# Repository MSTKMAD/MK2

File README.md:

# Proyecto de Contruccion del 2º modelo de la MACHETE (MK2)

Este reopsitorio es un Fork qe proviene del respositorio de bitbucket de la EDCPSU.
Las versiones HW de partida son la r15 para la tarjeta de la EDCPSU
Las versiones SW de partida son la 730 para el codigo de la DUAL y la version 731 de la EDCPSU o Main.

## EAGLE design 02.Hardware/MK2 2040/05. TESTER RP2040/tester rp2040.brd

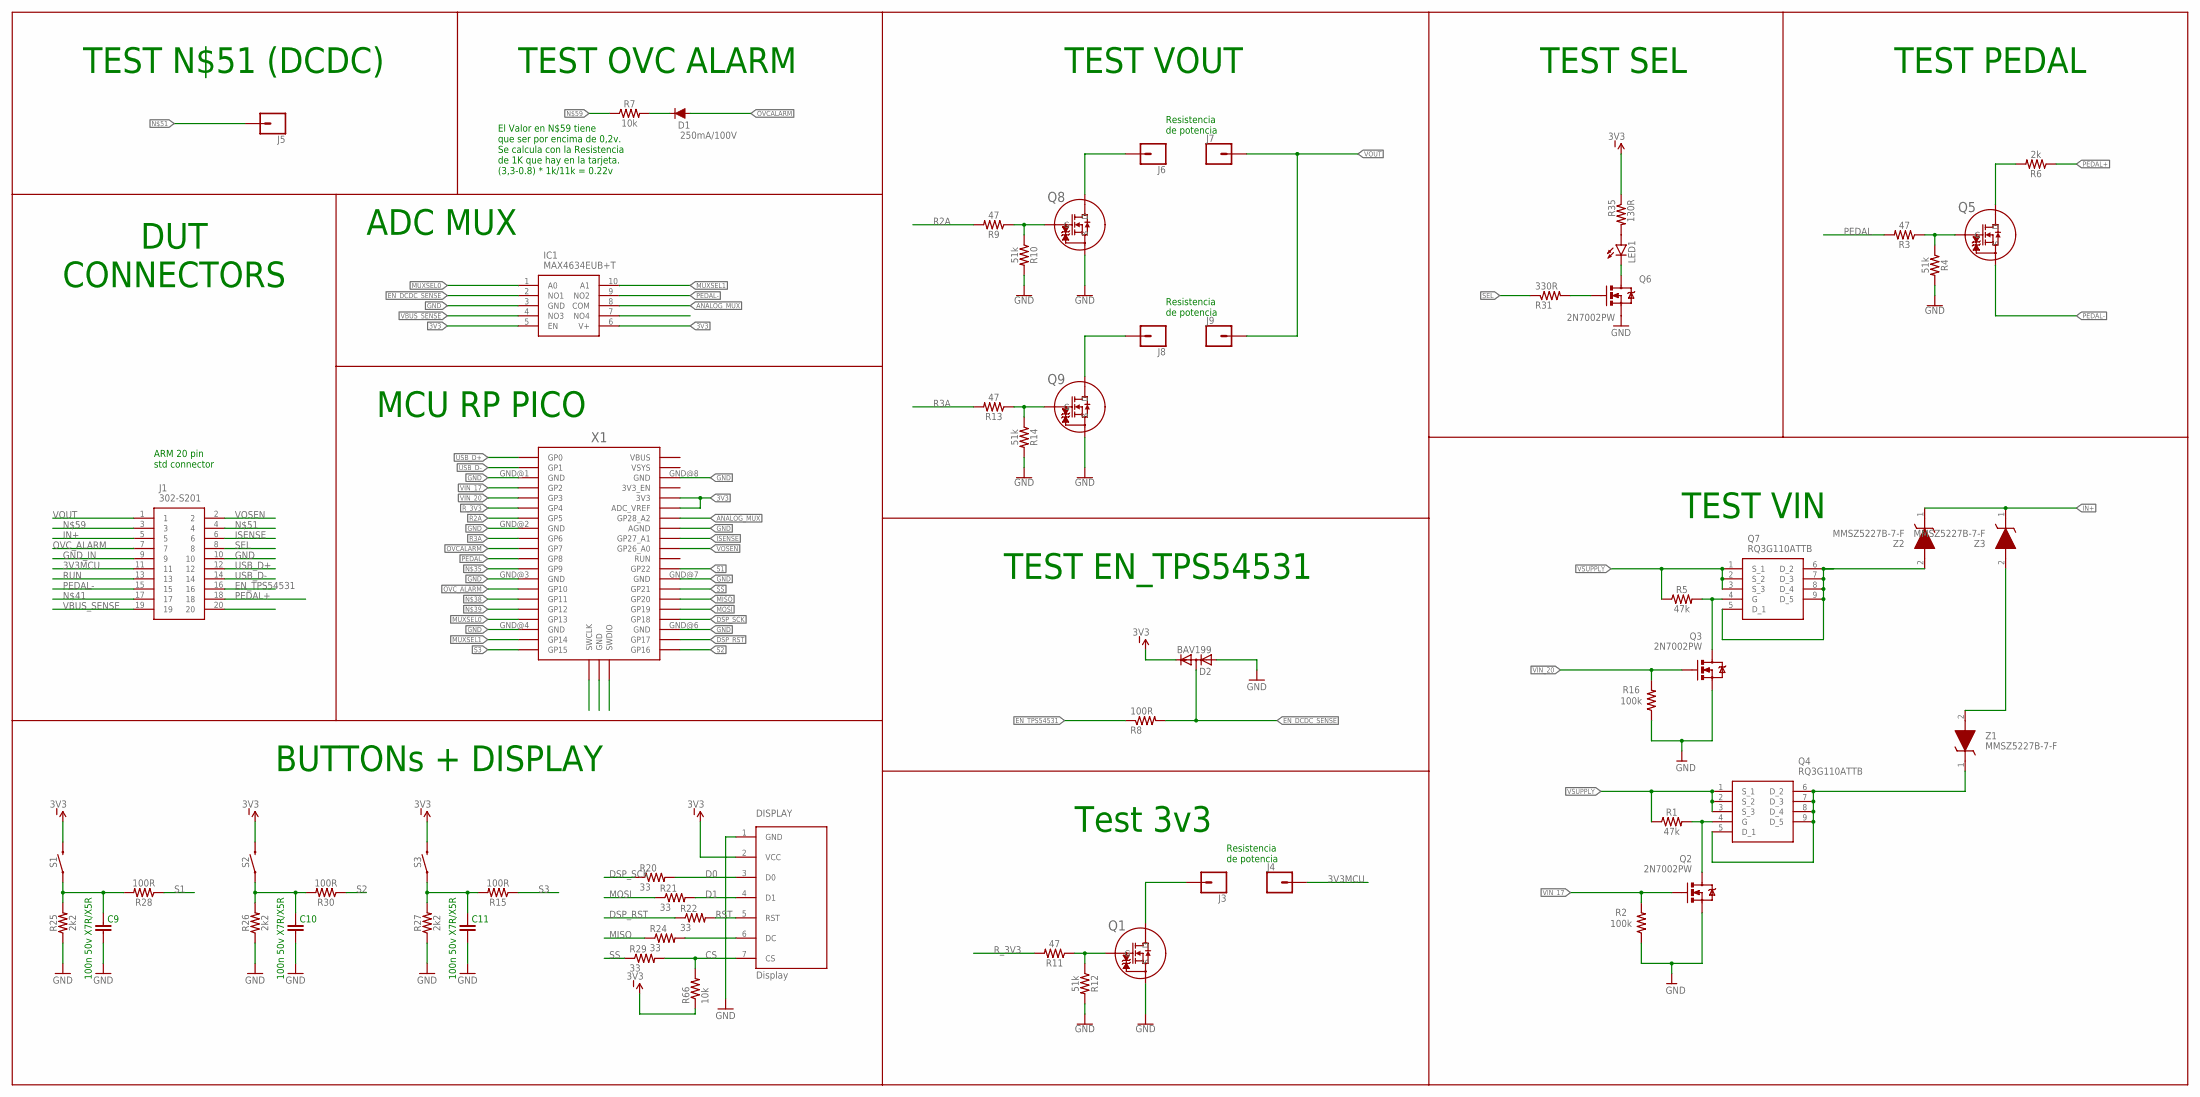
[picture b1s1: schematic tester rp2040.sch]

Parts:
C9, C10, C11: 100n 50v X7R/X5R; 0805
D1: 250mA/100V; SOD-323
D2: BAV199; SOT23
DISPLAY: Display; OLED_LCD
IC1: MAX4634EUB+T; SOP50P490X110-10N
J1: 302-S201; SHDR20W66P254_2X10_3300X905X90
J3, J4, J5, J6, J7, J8, J9: CONN_01; 1X01
LED1: LED3MM
Q1, Q5, Q8, Q9: PJA3416AE_R1_00001; SOT23_PJA3416_PNJ
Q2, Q3, Q6: 2N7002PW; SOT323
Q4, Q7: RQ3G110ATTB
R1, R5: 47k; 0402
R2, R16: 100k; 0402
R3, R9, R11, R13: 47; 0805
R4, R10, R12, R14: 51k; 0805
R6: 2k; 0805
R7, R66: 10k; 0805
R8, R15, R28, R30: 100R; 0805
R20, R21, R22, R24, R29: 33; 0805
R25, R26, R27: 2k2; 0805
R31: 330R; 0805
R35: 130R; 0805
S1, S2, S3: MOMENTARY-SWITCH-SPST-SMD-5.2MM; TACTILE_SWITCH_SMD_5.2MM
X1: RPI_PICO_IG-TH; RPI_PICO_TH
Z1, Z2, Z3: MMSZ5227B-7-F; SOD3716X135N

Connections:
3V3: D2.2 (C), DISPLAY.2 (VCC), IC1.5 (EN), IC1.6 (V+), R35.1, R66.1, S1.3 (2), S2.3 (2), S3.3 (2), X1.3V3, X1.ADC_VREF
3V3MCU: J1.11, J4.1
ANALOG_MUX: IC1.8 (COM), X1.GP28_A2
CS: DISPLAY.7 (CS), R29.2, R66.2
D0: DISPLAY.3 (D0), R20.2
D1: DISPLAY.4 (D1), R21.2
DSP_RST: R22.1, X1.GP17
DSP_SCK: R20.1, X1.GP18
EN_DCDC_SENSE: D2.3 (AC), IC1.2 (NO1), R8.2
EN_TPS54531: J1.16, R8.1
GND: C9.1, C10.1, C11.1, D2.1 (A), DISPLAY.1 (GND), IC1.3 (GND), J1.10, Q1.2 (S), Q2.2 (S), Q3.2 (S), Q6.2 (S), Q8.2 (S), Q9.2 (S), R2.1, R4.2, R10.2, R12.2, R14.2, R16.1, R25.1, R26.1, R27.1, X1.AGND, X1.GND@1 (GND), X1.GND@2 (GND), X1.GND@3 (GND), X1.GND@4 (GND), X1.GND@6 (GND), X1.GND@7 (GND), X1.GND@8 (GND)
GND_IN: J1.9
IN+: J1.5, Q7.5 (D_1), Q7.6 (D_2), Q7.7 (D_3), Q7.8 (D_4), Q7.9 (D_5), Z2.1 (K), Z2.2 (A), Z3.1 (K)
ISENSE: J1.6, X1.GP27_A1
MISO: R24.1, X1.GP20
MOSI: R21.1, X1.GP19
MUXSEL0: IC1.1 (A0), X1.GP13
MUXSEL1: IC1.10 (A1), X1.GP14
unnamed: J3.1, Q1.3 (D)
unnamed: Z1.2 (A), Z3.2 (A)
unnamed: Q3.3 (D), Q7.4 (G), R5.2
unnamed: D1.C, R7.2
unnamed: Q2.3 (D), Q4.4 (G), R1.2
unnamed: DISPLAY.6 (DC), R24.2
unnamed: Q5.1 (G), R3.1, R4.1
unnamed: Q4.5 (D_1), Q4.6 (D_2), Q4.7 (D_3), Q4.8 (D_4), Q4.9 (D_5), Z1.1 (K)
unnamed: Q1.1 (G), R11.1, R12.1
unnamed: Q5.3 (D), R6.2
unnamed: Q6.1 (G), R31.2
unnamed: LED1.A, R35.2
unnamed: LED1.K (C), Q6.3 (D)
unnamed: Q8.1 (G), R9.1, R10.1
unnamed: J6.1, Q8.3 (D)
unnamed: Q9.1 (G), R13.1, R14.1
unnamed: J8.1, Q9.3 (D)
unnamed: C9.2, R25.2, R28.2, S1.1
unnamed: C10.2, R26.2, R30.2, S2.1
unnamed: J1.4, J5.1
unnamed: C11.2, R15.2, R27.2, S3.1
unnamed: J1.3, R7.1
OVCALARM: D1.A, X1.GP7
OVC_ALARM: J1.7, X1.GP10
PEDAL: R3.2, X1.GP8
PEDAL+: J1.18, R6.1
PEDAL-: IC1.9 (NO2), J1.15, Q5.2 (S)
R2A: R9.2, X1.GP5
R3A: R13.2, X1.GP6
RST: DISPLAY.5 (RST), R22.2
RUN: J1.13
R_3V3: R11.2, X1.GP4
S1: R28.1, X1.GP22
S2: R30.1, X1.GP16
S3: R15.1, X1.GP15
SEL: J1.8, R31.1
SS: R29.1, X1.GP21
USB_D+: J1.12, X1.GP0
USB_D-: J1.14, X1.GP1
VBUS_SENSE: IC1.4 (NO3), J1.19
VIN_17: Q2.1 (G), R2.2, X1.GP2
VIN_20: Q3.1 (G), R16.2, X1.GP3
VOSEN: J1.2, X1.GP26_A0
VOUT: J1.1, J7.1, J9.1
VSUPPLY: Q4.1 (S_1), Q4.2 (S_2), Q4.3 (S_3), Q7.1 (S_1), Q7.2 (S_2), Q7.3 (S_3), R1.1, R5.1

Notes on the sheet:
ARM 20 pin std connector
Resistencia de potencia
Test 3v3
TEST VIN
TEST PEDAL
TEST OVC ALARM
TEST N$51 (DCDC)
TEST SEL
TEST EN_TPS54531
TEST VOUT
ADC MUX
MCU RP PICO
DUT CONNECTORS
BUTTONs + DISPLAY
El Valor en N$59 tiene que ser por encima de 0,2v. Se calcula con la Resistencia de 1K que hay en la tarjeta. (3,3-0.8) * 1k/11k = 0.22v

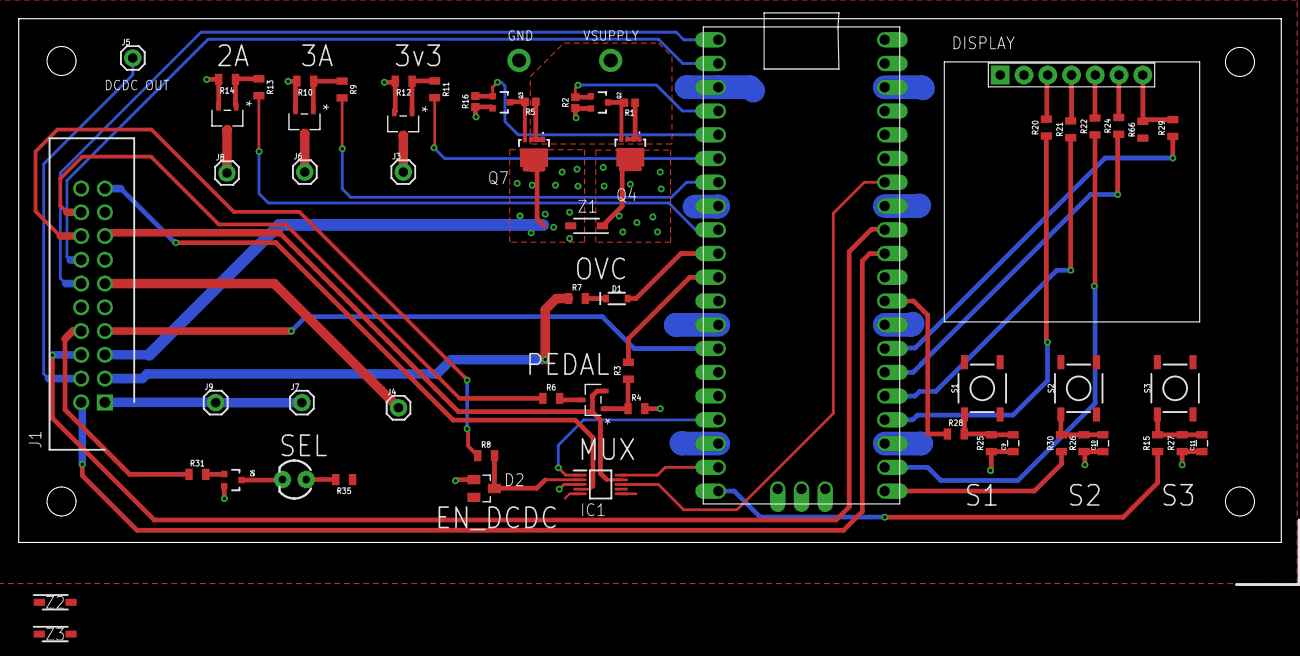
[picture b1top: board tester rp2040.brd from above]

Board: 2 copper layers, 135.0 x 56.0 mm, 61 parts (0 on the bottom side), 61 nets.

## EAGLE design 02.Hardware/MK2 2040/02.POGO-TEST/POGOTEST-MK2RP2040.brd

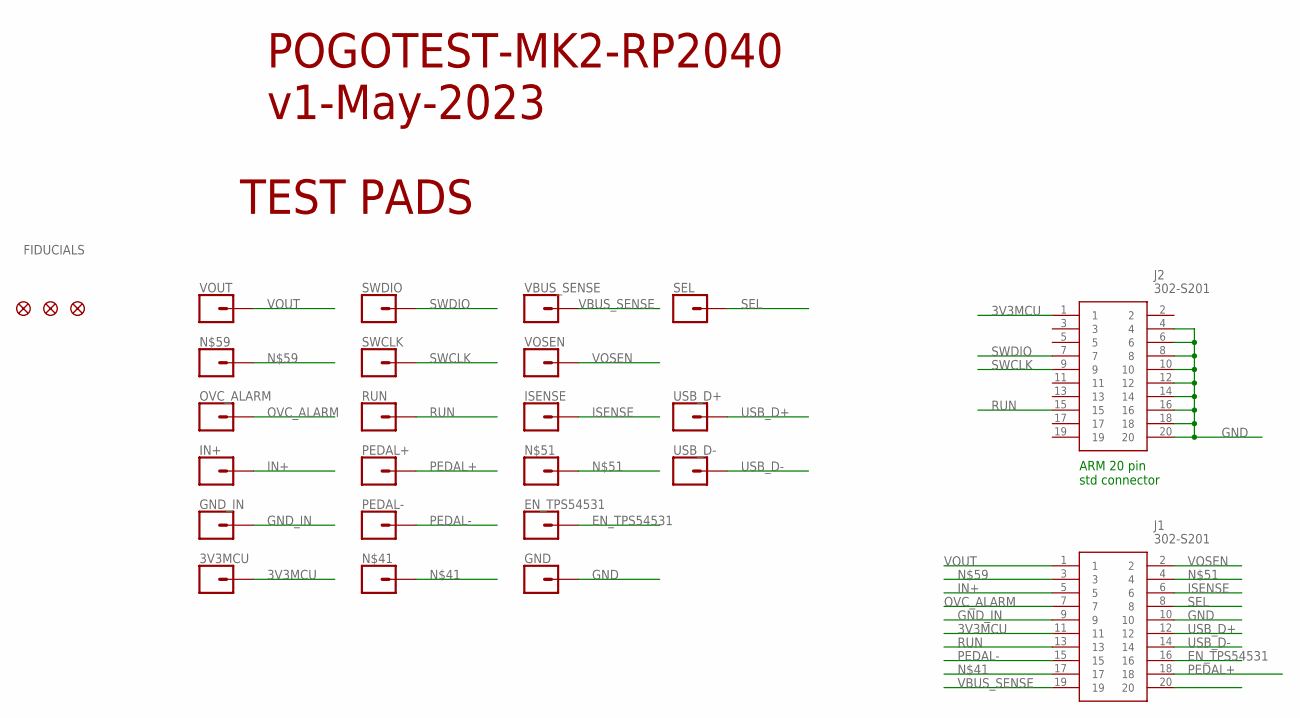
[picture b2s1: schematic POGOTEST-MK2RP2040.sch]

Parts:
3V3MCU: CONN_01POGOPIN_HOLE_LARGE; 1X01_POGOPIN_HOLE_0.061_DIA
EN_TPS54531: CONN_01POGOPIN_HOLE_LARGE; 1X01_POGOPIN_HOLE_0.061_DIA
FID3, FID5, FID6: FIDUCIAL1X2; FIDUCIAL-1X2
GND: CONN_01POGOPIN_HOLE_LARGE; 1X01_POGOPIN_HOLE_0.061_DIA
GND_IN: CONN_01POGOPIN_HOLE_LARGE; 1X01_POGOPIN_HOLE_0.061_DIA
IN+: CONN_01POGOPIN_HOLE_LARGE; 1X01_POGOPIN_HOLE_0.061_DIA
ISENSE: CONN_01POGOPIN_HOLE_LARGE; 1X01_POGOPIN_HOLE_0.061_DIA
J1, J2: 302-S201; SHDR20W66P254_2X10_3300X905X90
N$41, N$51, N$59: CONN_01POGOPIN_HOLE_LARGE; 1X01_POGOPIN_HOLE_0.061_DIA
OVC_ALARM: CONN_01POGOPIN_HOLE_LARGE; 1X01_POGOPIN_HOLE_0.061_DIA
PEDAL+: CONN_01POGOPIN_HOLE_LARGE; 1X01_POGOPIN_HOLE_0.061_DIA
PEDAL-: CONN_01POGOPIN_HOLE_LARGE; 1X01_POGOPIN_HOLE_0.061_DIA
RUN: CONN_01POGOPIN_HOLE_LARGE; 1X01_POGOPIN_HOLE_0.061_DIA
SEL: CONN_01POGOPIN_HOLE_LARGE; 1X01_POGOPIN_HOLE_0.061_DIA
SWCLK: CONN_01POGOPIN_HOLE_LARGE; 1X01_POGOPIN_HOLE_0.061_DIA
SWDIO: CONN_01POGOPIN_HOLE_LARGE; 1X01_POGOPIN_HOLE_0.061_DIA
USB_D+: CONN_01POGOPIN_HOLE_LARGE; 1X01_POGOPIN_HOLE_0.061_DIA
USB_D-: CONN_01POGOPIN_HOLE_LARGE; 1X01_POGOPIN_HOLE_0.061_DIA
VBUS_SENSE: CONN_01POGOPIN_HOLE_LARGE; 1X01_POGOPIN_HOLE_0.061_DIA
VOSEN: CONN_01POGOPIN_HOLE_LARGE; 1X01_POGOPIN_HOLE_0.061_DIA
VOUT: CONN_01POGOPIN_HOLE_LARGE; 1X01_POGOPIN_HOLE_0.061_DIA

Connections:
3V3MCU: 3V3MCU.2, J1.11, J2.1
EN_TPS54531: EN_TPS54531.2, J1.16
GND: GND.2, J1.10, J2.4, J2.6, J2.8, J2.10, J2.12, J2.14, J2.16, J2.18, J2.20
GND_IN: GND_IN.2, J1.9
IN+: IN+.2, J1.5
ISENSE: ISENSE.2, J1.6
unnamed: J1.17, N$41.2
unnamed: J1.4, N$51.2
unnamed: J1.3, N$59.2
OVC_ALARM: J1.7, OVC_ALARM.2
PEDAL+: J1.18, PEDAL+.2
PEDAL-: J1.15, PEDAL-.2
RUN: J1.13, J2.15, RUN.2
SEL: J1.8, SEL.2
SWCLK: J2.9, SWCLK.2
SWDIO: J2.7, SWDIO.2
USB_D+: J1.12, USB_D+.2
USB_D-: J1.14, USB_D-.2
VBUS_SENSE: J1.19, VBUS_SENSE.2
VOSEN: J1.2, VOSEN.2
VOUT: J1.1, VOUT.2

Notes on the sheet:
TEST PADS
POGOTEST-MK2-RP2040 v1-May-2023
FIDUCIALS
ARM 20 pin std connector

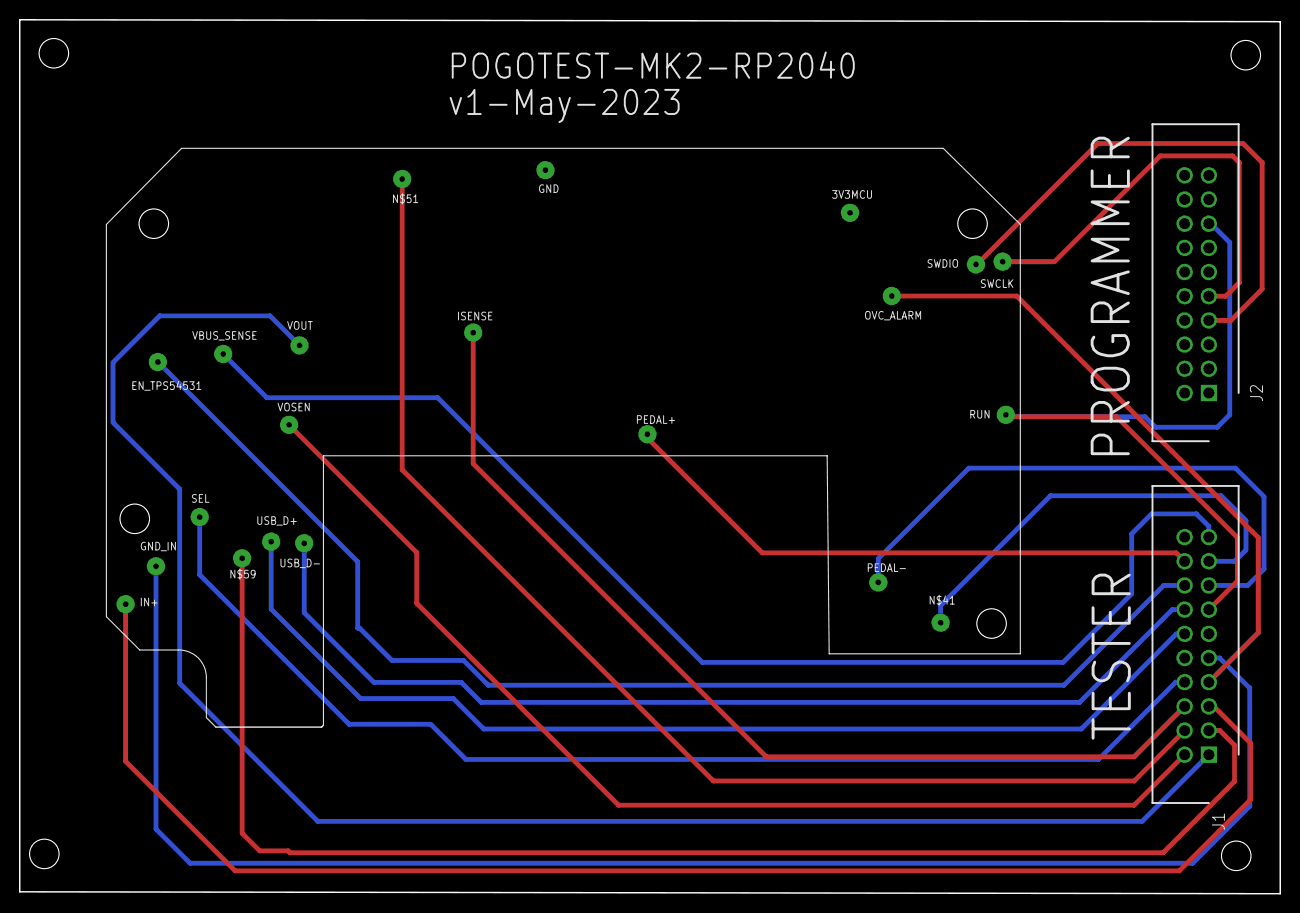
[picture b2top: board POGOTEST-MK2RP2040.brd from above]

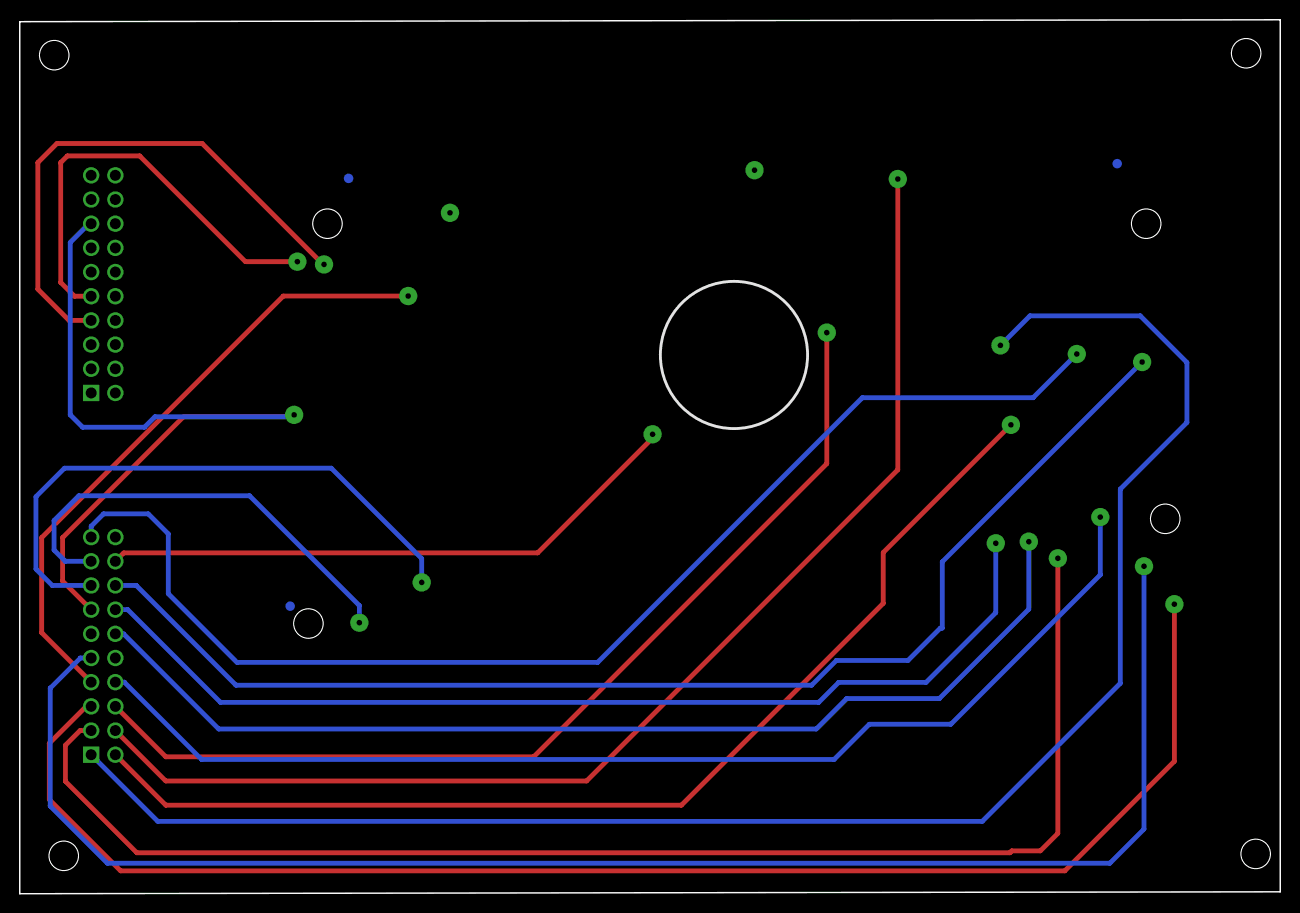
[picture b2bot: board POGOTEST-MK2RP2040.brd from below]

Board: 2 copper layers, 132.4 x 91.8 mm, 26 parts (3 on the bottom side), 21 nets.

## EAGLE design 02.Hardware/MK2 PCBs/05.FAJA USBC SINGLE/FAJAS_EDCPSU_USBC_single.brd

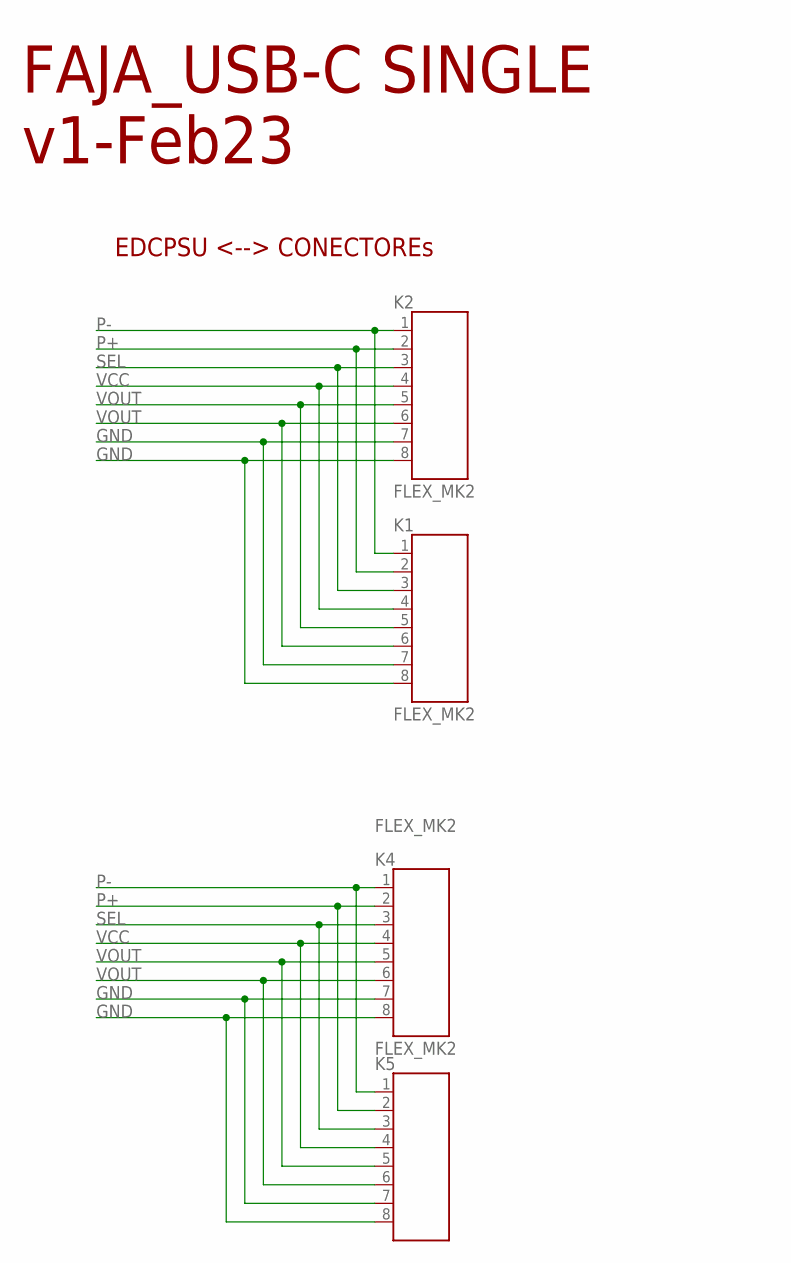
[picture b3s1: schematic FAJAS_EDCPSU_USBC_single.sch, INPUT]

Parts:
K1, K2, K4, K5: FLEX_MK2; FLEX8

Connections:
GND: K1.7, K1.8, K2.7, K2.8, K4.7, K4.8, K5.7, K5.8
P+: K1.2, K2.2, K4.2, K5.2
P-: K1.1, K2.1, K4.1, K5.1
SEL: K1.3, K2.3, K4.3, K5.3
VCC: K1.4, K2.4, K4.4, K5.4
VOUT: K1.5, K1.6, K2.5, K2.6, K4.5, K4.6, K5.5, K5.6

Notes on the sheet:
FAJA_USB-C SINGLE v1-Feb23
EDCPSU <--> CONECTOREs

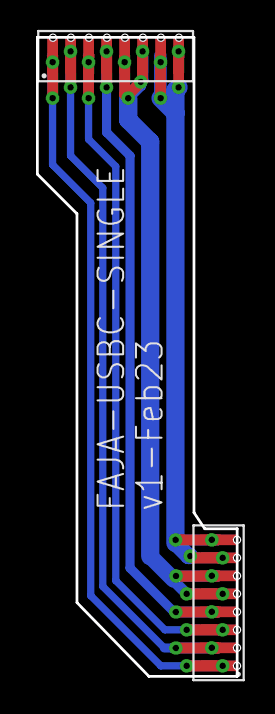
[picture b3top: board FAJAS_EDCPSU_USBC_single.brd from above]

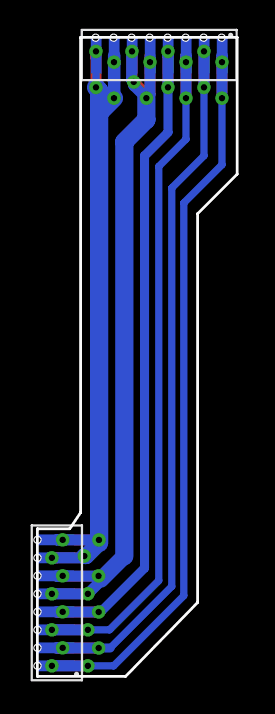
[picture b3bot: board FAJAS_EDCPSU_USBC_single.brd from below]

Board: 2 copper layers, 11.1 x 35.5 mm, 4 parts (2 on the bottom side), 6 nets.

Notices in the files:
parts and their libraries:
SparkFun-Electromechanical: Licensing: Creative Commons ShareAlike 4.0 International - https://creativecommons.org/licenses/by-sa/4.0
SparkFun-DiscreteSemi: Licensing: CC v3.0 Share-Alike You are welcome to use this library for commercial purposes.
